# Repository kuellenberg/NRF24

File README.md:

# NRF24

Wireless temperature and humidity transmitter using the nRF24L01+

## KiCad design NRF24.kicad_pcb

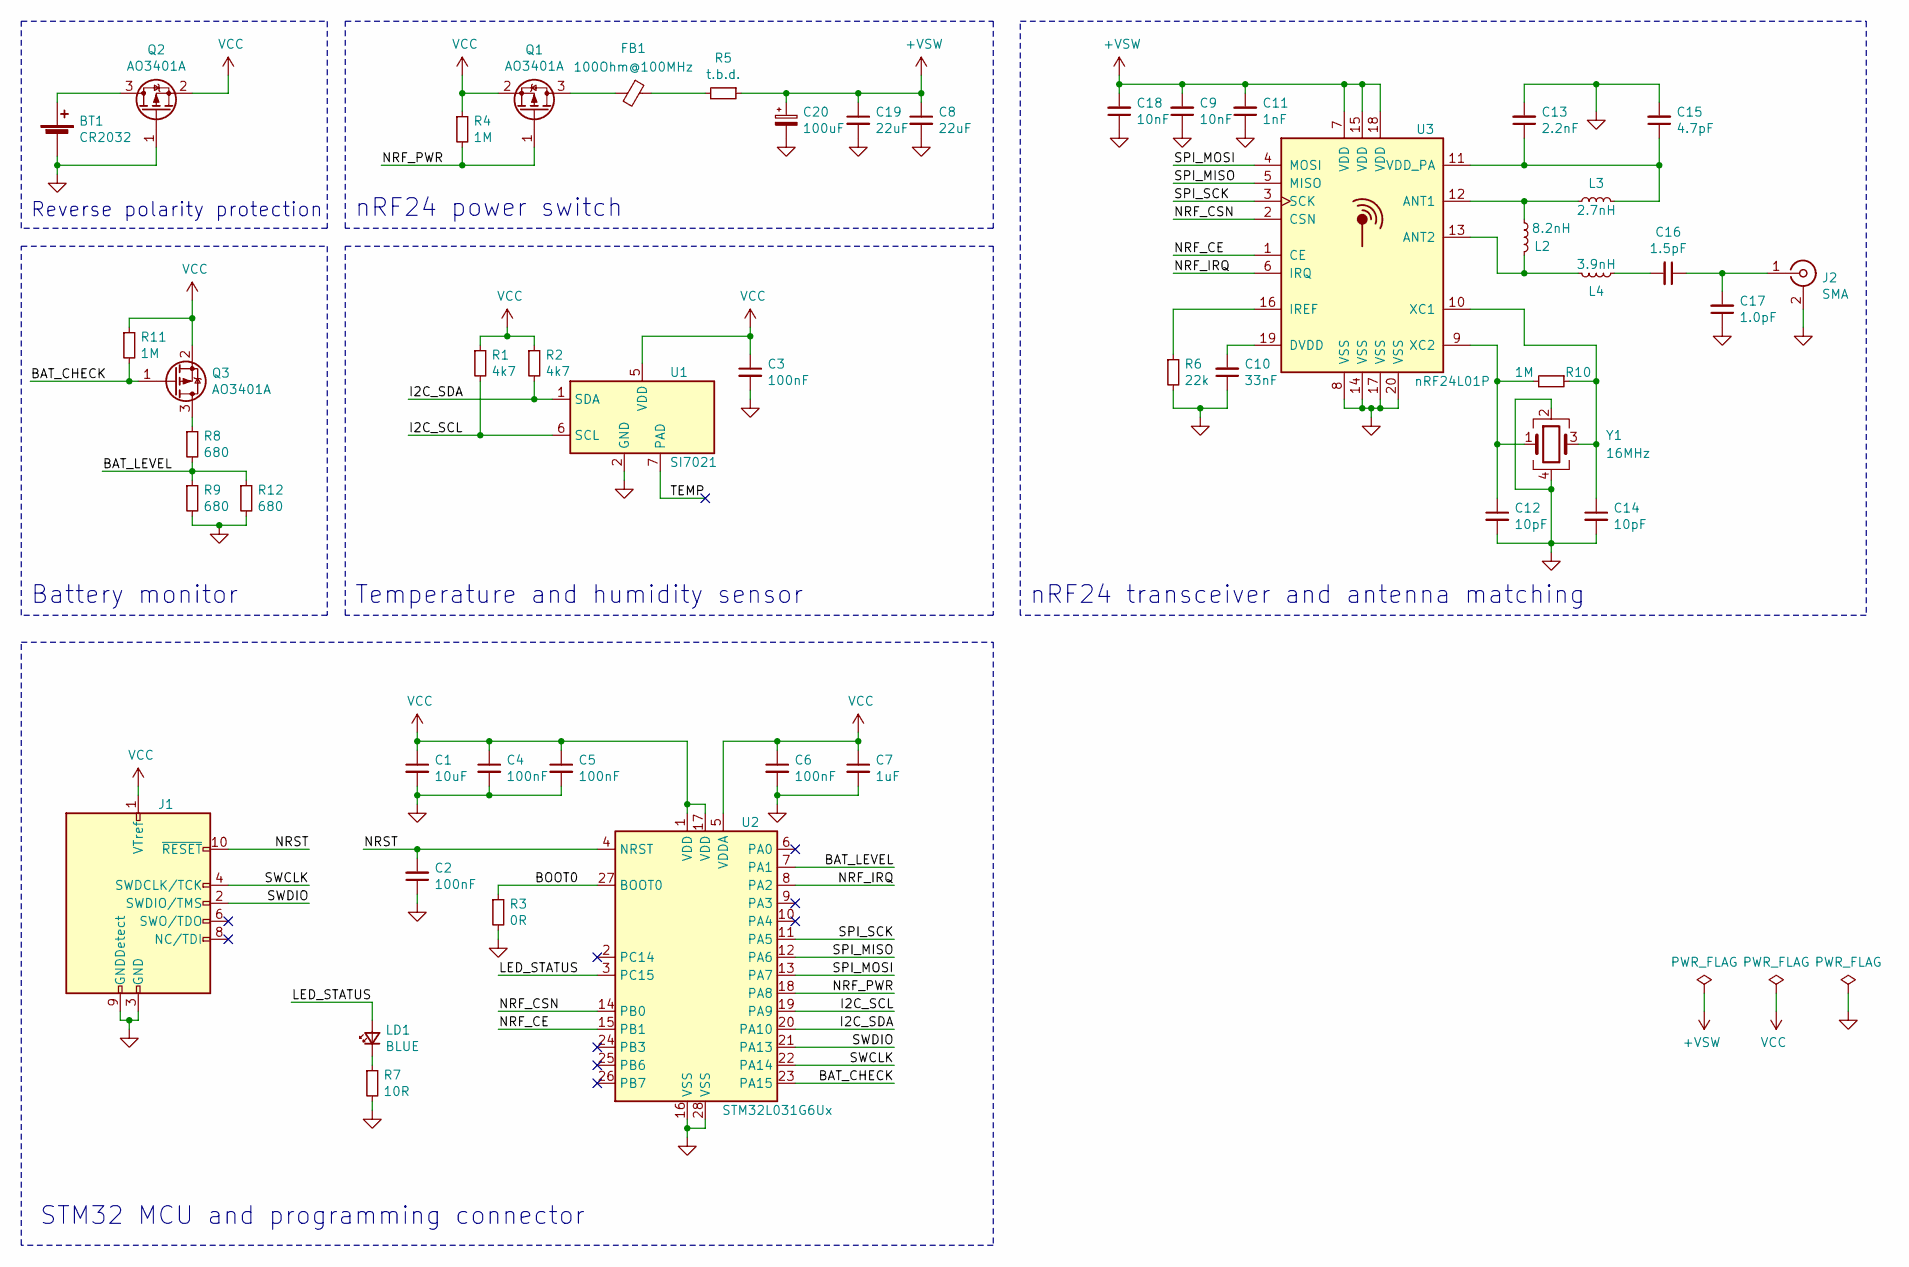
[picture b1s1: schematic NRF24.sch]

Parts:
BT1: CR2032; BatteryHolder_Keystone_1060_1x2032; Mouser 534-1060TR
C1: 10uF; C_0603_1608Metric; LCSC C19702
C2, C3, C4, C5, C6: 100nF; C_0402_1005Metric; LCSC C1525
C7: 1uF; C_0603_1608Metric; LCSC C15849
C8, C19: 22uF; C_0603_1608Metric; LCSC C59461
C9, C18: 10nF; C_0402_1005Metric; LCSC C15195
C10: 33nF; C_0402_1005Metric; LCSC C1585
C11: 1nF; C_0402_1005Metric; LCSC C1523
C12, C14: 10pF; C_0402_1005Metric; LCSC C32949
C13: 2.2nF; C_0402_1005Metric; LCSC C1531
C15: 4.7pF; C_0402_1005Metric; LCSC C1569
C16: 1.5pF; C_0402_1005Metric; LCSC C1552
C17: 1.0pF; C_0402_1005Metric; LCSC C1550
C20: 100uF; CP_EIA-3528-15_AVX-H; LCSC C16133
FB1: 100Ohm@100MHz; L_0805_2012Metric; LCSC C1015
J1: Conn_ARM_JTAG_SWD_10; PinHeader_2x05_P1.27mm_Vertical_SMD; Mouser 855-M50-3610542R
J2: SMA; SMA_Samtec_SMA-J-P-H-ST-EM1_EdgeMount; Mouser 200-SMAJPHSTEM1
L2: 8.2nH; L_0402_1005Metric; LCSC C16208
L3: 2.7nH; L_0402_1005Metric; LCSC C27123
L4: 3.9nH; L_0402_1005Metric; LCSC C14033
LD1: BLUE; LED_0603_1608Metric; LCSC LED_0603
Q1, Q2, Q3: AO3401A; SOT-23; LCSC C15127
R1, R2: 4k7; R_0402_1005Metric; LCSC C25900
R3: 0R; R_0402_1005Metric; LCSC C17168
R4, R10, R11: 1M; R_0402_1005Metric; LCSC C26083
R5: t.b.d.; R_0402_1005Metric; LCSC C11702
R6: 22k; R_0402_1005Metric; LCSC C25768
R7: 10R; R_0402_1005Metric; LCSC C25077
R8, R9, R12: 680; R_0402_1005Metric; LCSC C25130
U1: SI7021; DFN-6-1EP_3x3mm_P1mm_EP1.5x2.4mm; LCSC C132603
U2: STM32L031G6Ux; QFN-28_4x4mm_P0.5mm; LCSC C96514
U3: nRF24L01P; QFN-20-1EP_4x4mm_P0.5mm_EP2.5x2.5mm; LCSC C8791
Y1: 16MHz; Crystal_SMD_3225-4Pin_3.2x2.5mm; LCSC C13738

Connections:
+VSW: C8.1, C9.2, C11.2, C18.2, C19.1, C20.1, R5.1, U3.7 (VDD), U3.15 (VDD), U3.18 (VDD)
/BAT_CHECK: Q3.1 (G), R11.2, U2.23 (PA15)
/BAT_LEVEL: R8.2, R9.1, R12.1, U2.7 (PA1)
/BOOT0: R3.1, U2.27 (BOOT0)
/I2C_SCL: R1.2, U1.6 (SCL), U2.19 (PA9)
/I2C_SDA: R2.2, U1.1 (SDA), U2.20 (PA10)
/LED_STATUS: LD1.2 (A), U2.3 (PC15)
/NRF_CE: U2.15 (PB1), U3.1 (CE)
/NRF_CSN: U2.14 (PB0), U3.2 (CSN)
/NRF_IRQ: U2.8 (PA2), U3.6 (IRQ)
/NRF_PWR: Q1.1 (G), R4.2, U2.18 (PA8)
/NRST: C2.2, J1.10 (~RESET~), U2.4 (NRST)
/SPI_MISO: U2.12 (PA6), U3.5 (MISO)
/SPI_MOSI: U2.13 (PA7), U3.4 (MOSI)
/SPI_SCK: U2.11 (PA5), U3.3 (SCK)
/SWCLK: J1.4 (SWDCLK/TCK), U2.22 (PA14)
/SWDIO: J1.2 (SWDIO/TMS), U2.21 (PA13)
/TEMP: U1.7 (PAD)
GND: BT1.2 (-), C1.2, C2.1, C3.2, C4.2, C5.2, C6.2, C7.2, C8.2, C9.1, C10.1, C11.1, C12.2, C13.2, C14.2, C15.2, C17.1, C18.1, C19.2, C20.2, J1.3 (GND), J1.5 (GND), J1.9 (GNDDetect), J2.2 (Ext), Q2.1 (G), R3.2, R6.2, R7.2, R9.2, R12.2, U1.2 (GND), U2.16 (VSS), U2.28 (VSS), U3.8 (VSS), U3.14 (VSS), U3.17 (VSS), U3.20 (VSS), U3.21, Y1.2, Y1.4
unnamed: BT1.1 (+), Q2.3 (D)
unnamed: C10.2, U3.19 (DVDD)
unnamed: C12.1, R10.2, U3.9 (XC2), Y1.1
unnamed: C13.1, C15.1, L3.2, U3.11 (VDD_PA)
unnamed: C14.1, R10.1, U3.10 (XC1), Y1.3
unnamed: C16.1, C17.2, J2.1 (In)
unnamed: C16.2, L4.1
unnamed: FB1.1, R5.2
unnamed: FB1.2, Q1.3 (D)
unnamed: L2.1, L3.1, U3.12 (ANT1)
unnamed: L2.2, L4.2, U3.13 (ANT2)
unnamed: LD1.1 (K), R7.1
unnamed: Q3.3 (D), R8.1
unnamed: R6.1, U3.16 (IREF)
VCC: C1.1, C3.1, C4.1, C5.1, C6.1, C7.1, J1.1 (VTref), Q1.2 (S), Q2.2 (S), Q3.2 (S), R1.1, R2.1, R4.1, R11.1, U1.5 (VDD), U2.1 (VDD), U2.5 (VDDA), U2.17 (VDD)

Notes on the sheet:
nRF24 transceiver and antenna matching
Temperature and humidity sensor
Battery monitor
Reverse polarity protection
nRF24 power switch
STM32 MCU and programming connector

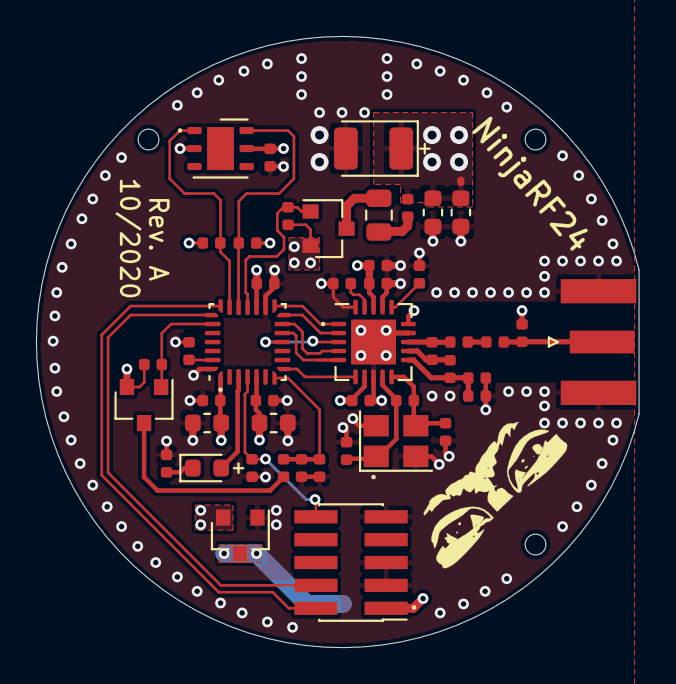
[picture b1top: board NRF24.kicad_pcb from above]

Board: 4 copper layers, 33.5 x 34.0 mm, 47 parts (1 on the bottom side), 33 nets.

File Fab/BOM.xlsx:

Designator | Comment | Footprint | LCSC Part #
C1 | 10uF | 0603_C
C2, C3, C4, C5, C6 | 100nF | 0402_C
C7 | 1uF | 0603_C
C9, C18 | 10nF | 0402_C
C10 | 33nF | 0402_C
C11 | 1nF | 0402_C
C12, C14 | 22pF | 0402_C
C13 | 2.2nF | 0402_C
C15 | 4.7pF | 0402_C
C16 | 1.5pF | 0402_C
C17 | 1.0pF | 0402_C
FB1 | 100 @ 100MHz | 0402_L
L2 | 8.2nH | 0402_L
L3 | 2.7nH | 0402_L
L4 | 3.9nH | 0402_L
LD1 | BLUE | 0402
Q1, Q2 | NTK3139P | Package_TO_SOT_SMD:SOT-723
R1, R2 | 4k7 | 0402_R
R3 | 0R | 0402_R
R4, R10 | 1M | 0402_R
R5, R8, R9 | TBD | 0402_R
R6 | 22k | 0402_R
R7 | 10R | 0402_R
U1 | Si7021-A20 | Package_DFN_QFN:DFN-6-1EP_3x3mm_P1mm_EP1.5x2.4mm
U2 | STM32L031G6Ux | Package_DFN_QFN:QFN-28_4x4mm_P0.5mm
U3 | nRF24L01P | Package_DFN_QFN:QFN-20-1EP_4x4mm_P0.5mm_EP2.5x2.5mm
Y1 | 16MHz | Crystal:Crystal_SMD_3225-4Pin_3.2x2.5mm

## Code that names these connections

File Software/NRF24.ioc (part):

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Mcu.Name=STM32L031G(4-6)Ux
Mcu.Package=UFQFPN28
Mcu.UserName=STM32L031G6Ux
PA1.GPIOParameters=GPIO_Label
PA1.GPIO_Label=BAT_LEVEL
PA1.Mode=IN1
PA1.Signal=ADC_IN1
PA10.Mode=I2C
PA10.Signal=I2C1_SDA
PA13.Mode=Serial_Wire
PA13.Signal=SYS_SWDIO
PA14.Mode=Serial_Wire
PA14.Signal=SYS_SWCLK
PA15.GPIOParameters=GPIO_Label
PA15.GPIO_Label=BAT_CHECK
PA15.Signal=GPIO_Output
PA2.GPIOParameters=GPIO_Label
PA2.GPIO_Label=NRF_IRQ
PA2.Signal=GPIO_Input
PA5.Mode=Full_Duplex_Master
PA5.Signal=SPI1_SCK
PA6.Mode=Full_Duplex_Master
PA6.Signal=SPI1_MISO
PA7.Mode=Full_Duplex_Master
PA7.Signal=SPI1_MOSI
PA8.GPIOParameters=GPIO_Label
PA8.GPIO_Label=NRF_PWR
PA8.Signal=GPIO_Output
PA9.Mode=I2C
PA9.Signal=I2C1_SCL
PB0.GPIOParameters=GPIO_Label
PB0.GPIO_Label=NRF_CSN
PB0.Signal=GPIO_Output
PB1.GPIOParameters=GPIO_Label
PB1.GPIO_Label=NRF_CE
PB1.Signal=GPIO_Output
PC15-OSC32_OUT.GPIOParameters=GPIO_Label
PC15-OSC32_OUT.GPIO_Label=LED_STATUS
PC15-OSC32_OUT.Signal=GPIO_Output
RCC.HSE_VALUE=8000000
RCC.SYSCLKFreq_VALUE=2097000
board=custom

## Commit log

2020-09-27 Rough component placement
2020-09-28 Minor changes
2020-09-28 Layout
2020-10-02 Finalizing
2020-10-18 Firmware Blinky Test
2020-11-30 Firmware
2020-12-05 Updated schematic
